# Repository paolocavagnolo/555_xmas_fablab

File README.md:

# 555_xmas_fablab

## Cosa c'è nel mio kit ?!

| Nome          |Specifiche |  Q.tà |
|:--------------|:---------:|------:|
| Led           |  5mm      |    6  |
| Timer         |    555    |    1  |
| Condensatore  | 4uF       |    1  |
| resistenza 1  | 56 kOhm   |    1  |
| resistenza 2  | 1 kOhm    |    1  |
| resistenza 3  | 12 Ohm    |    1  |
| resistenza 4  | 1 kOhm    |    1  |
| batteria      | 1220 3V   |    1  |
| portabatteria | 3001      |    1  |

## A cosa servono

### 555
E' il timer più famoso di tutti. Leggete [qui](https://it.wikipedia.org/wiki/NE555) per approfondire.

### Condesatore
Il condesatore in questo circuito regola la velocità del lampeggio tra i led, un condesatore con una capacità più grande farà lampeggiare i led più lentamente. Prova!

### Resistenze e alimentazione
Le resistenze regolano la corrente nel circuito. Se usate la pila da 3V per alimentare il circuito vedrete che i led di destra sono più deboli di quelli di sinistra. Questo dipende anche dal valore delle resistenze.
Se collegate l'alimentazione alla 5V (tagliando un cavetto USB e collegando il filo nero al - e il filo rosso al +5V) dovrete cambiare valore delle resistenze per non danneggiare i led e avere una buona luminosità, questi sono dei buoni valori:

| Nome          | 5 Volt    |  Q.tà |
|---------------|:---------:|------:|
| resistenza 1  | 100 kOhm  |    1  |
| resistenza 2  | 1 kOhm    |    1  |
| resistenza 3  | 1 kOhm    |    1  |
| resistenza 4  | 1 kOhm    |    1  |

## Come si monta il kit?

Il kit è pronto per essere saldato, ti servirà un saldatore e dello stagno. Se non li hai ricevuti per regalo puoi provare a chiederli in prestito a qualcuno oppure venire al Fablab.

Se proprio non c'è nessuno che ti possa aiutare con le prime saldature puoi provare a cercare dei tutorial su youtube, ma qualcuno a fianco è più piacevole oltre che più sicuro.

### Saldare è l'unica possibilità?

Certo che no. Se hai intenzione di studiare il circuito cambiando componenti o valori delle resistenze è più facile usare una breadboard, la trovi in qualunque negozio di elettronica.

### Come è fatto il circuito?

Per il circuito abbiamo preso spunto da qui:
https://www.petervis.com/GCSE_Design_and_Technology_Electronic_Products/simple-555-circuits/555-timer-dual-led-flasher.html

riadattandolo per farlo funzionare con una pila da 3V

## Note

### Alimentazione e durata batteria
Questo circuito non nasce per lavorare a 3V, ma a 5V. A 3 è un po' al limite, quindi basta che la tensioni si abbassi un pochettino e il led non si accenderanno più.

Le batterie, man mano che si scaricano, abbassano leggermente la tensione. Nel nostro caso questo significa che con 6 Led rossi dopo circa un giorno di funzionamento continuo i led si spegneranno.

### Differenza di luminosità nei led
E' normale che i led di destra risultino meno luminosi di quelli di sinistra, è una caratteristica del circuito che funziona a 3V. Lavorando a 5V e modificando il valore delle resistenze funzionerà tutto bene!

### Bella la pcb, se volessi modificarla o produrla da me?
Nella cartella kiCad in questo repository trovi tutti i file che abbiamo usato per far produrre la pcb.

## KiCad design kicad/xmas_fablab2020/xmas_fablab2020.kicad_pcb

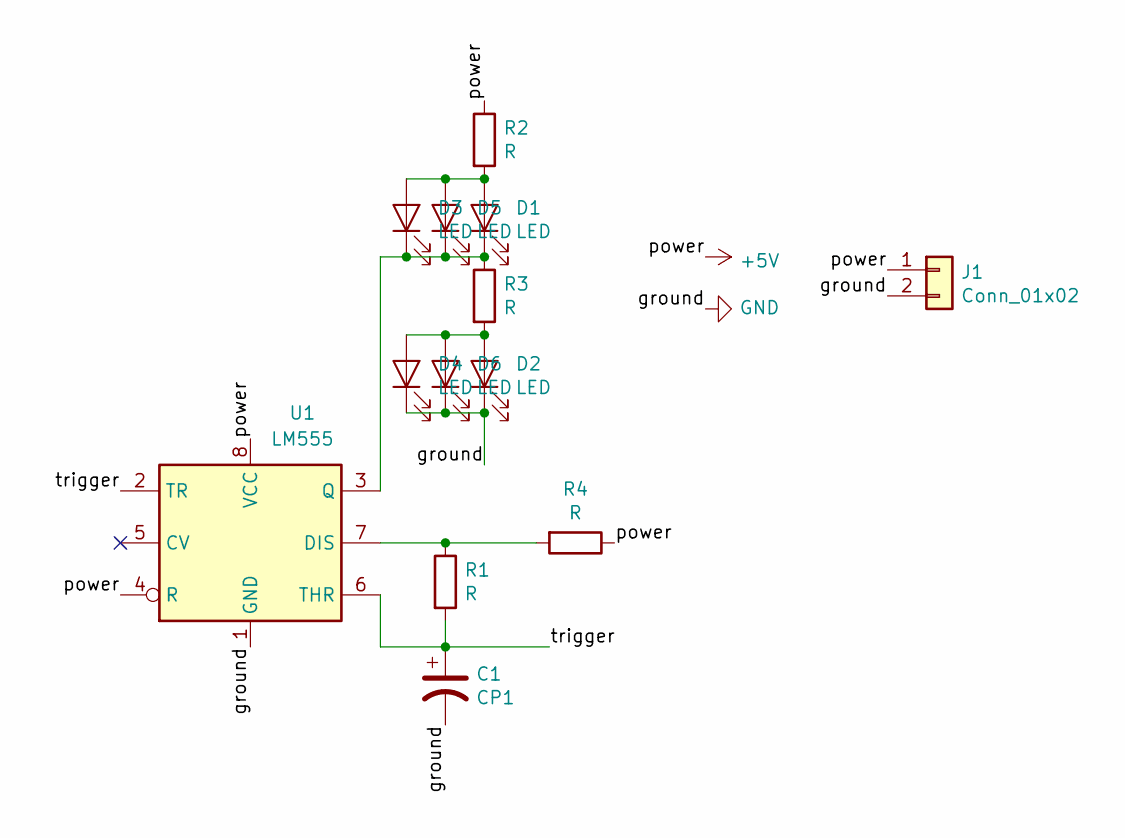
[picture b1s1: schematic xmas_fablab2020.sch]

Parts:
C1: CP1; CP_Radial_D6.3mm_P2.50mm
D1, D2, D3, D4, D5, D6: LED; LED_D5.0mm
J1: Conn_01x02; BatteryHolder_Keystone_3001_1x12mm
R1, R2, R3, R4: R; R_Axial_DIN0411_L9.9mm_D3.6mm_P20.32mm_Horizontal
U1: LM555; DIP-8_W7.62mm

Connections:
+5V: J1.1, R2.1, R4.1, U1.4 (R), U1.8 (VCC)
/trigger: C1.1, R1.2, U1.2 (TR), U1.6 (THR)
GND: C1.2, D2.1 (K), D4.1 (K), D6.1 (K), J1.2, U1.1 (GND)
unnamed: D1.1 (K), D3.1 (K), D5.1 (K), R3.1, U1.3 (Q)
unnamed: D1.2 (A), D3.2 (A), D5.2 (A), R2.2
unnamed: D2.2 (A), D4.2 (A), D6.2 (A), R3.2
unnamed: R1.1, R4.2, U1.7 (DIS)

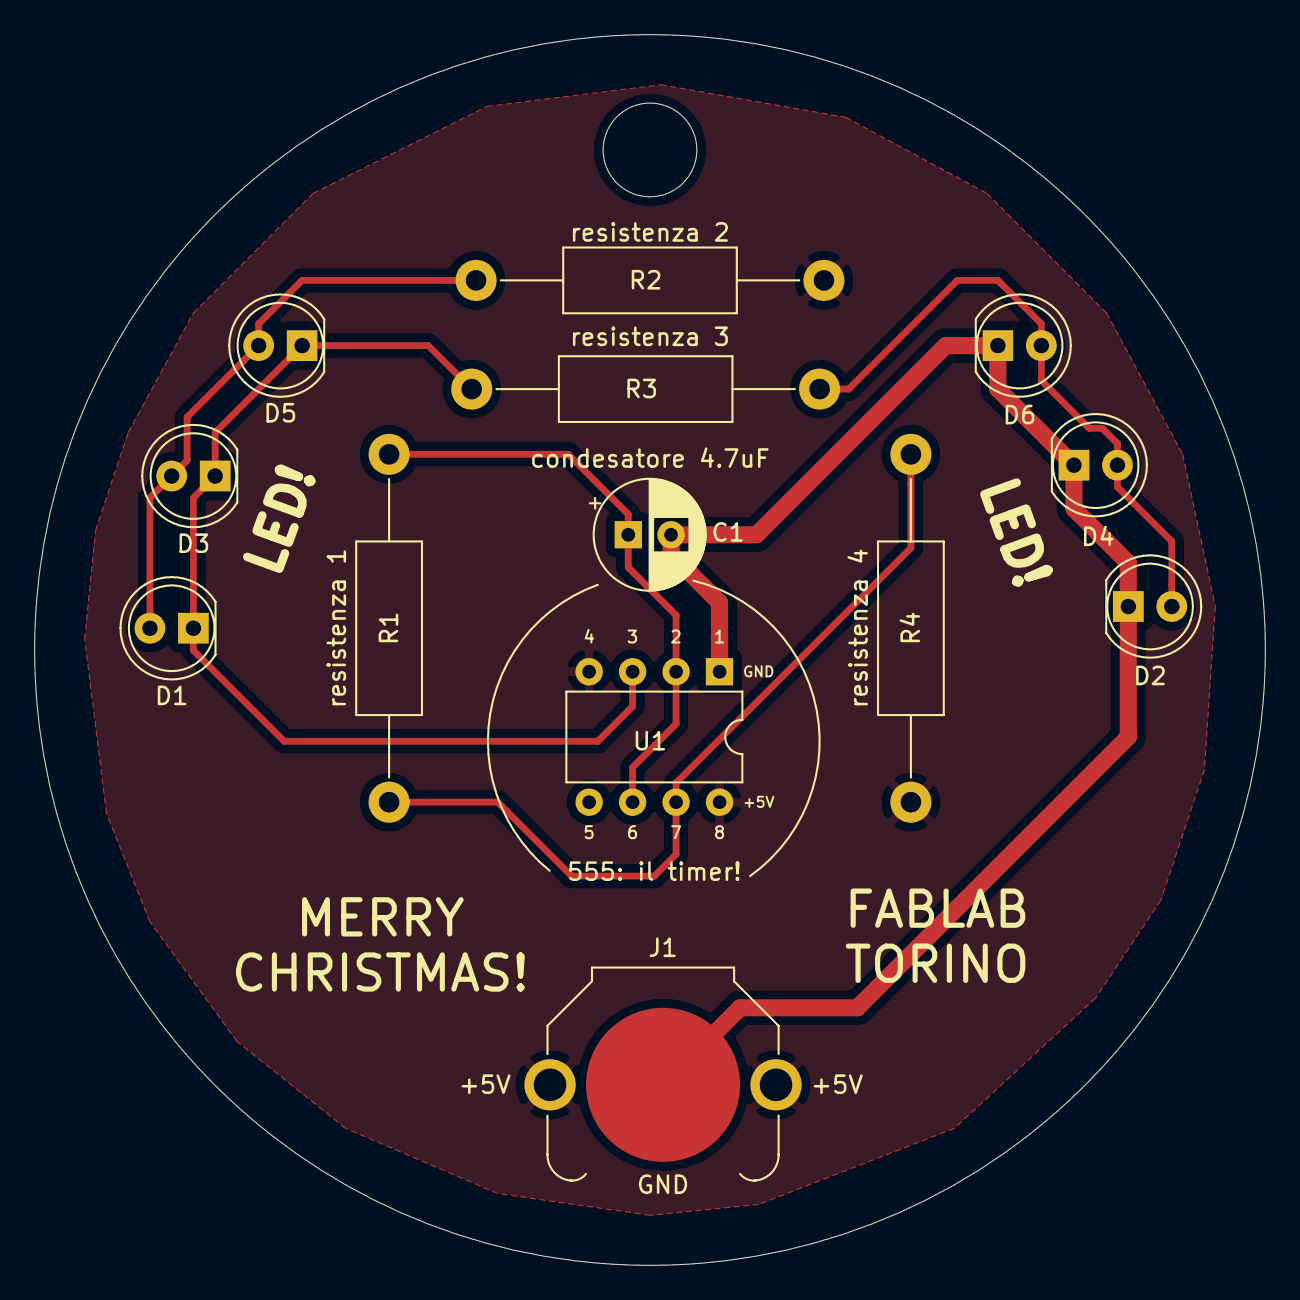
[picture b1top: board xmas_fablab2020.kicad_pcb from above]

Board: 2 copper layers, 71.9 x 71.9 mm, 13 parts (0 on the bottom side), 7 nets.

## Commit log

2020-12-14 Create test
